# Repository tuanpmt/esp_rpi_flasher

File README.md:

# ESP32 RPI FLASHER

Language: [Việt Nam](./README.vi.md)

## Introduction

When mass-producing ESP32's products we need to have the tool to load the program for the product as quickly as possible. We have several ways to optimize and speed up loading binary firmware for ESP32 as follows:
- Flash multiple products at the same time
- Reduce the binary size
- Speed ​​up the UART baudrate
- Automate loading steps (automatically into bootloader mode ...)

ESP RPI FLASHER is a set of ESP32 multi-board load support tools at the same time including:
- High-speed USB-UART CP2102 board, supporting baudrate speed up to 2Mbps
- The program running on Raspberry Pi can use multiple CP2102 at the same time

The features of the program run on Raspberri Pi as follows:
- Automatically identify the CP2102 that is being connected (can plug multiple via USB port)
- Change firmware for ESP32 easily with configuration file
- Allow reflash failed boards.

## Prepare
* [Raspberry Pi 3 Model B/B+](https://www.raspberrypi.org)
* Thẻ nhớ 16GB
* [CP2102 USB UART board](./esp32_cp_programmer)
* Micro USB Cable, Button, LED, PCB prototype.

**Functianal button and LED**

|  | Function |
|:---:|:---:|
| Flash Button | Click to flash the program |
| Reflash Button | Click to re-flash the failed board |
| Reboot Button | Click to restart Raspberry |
| Flash LED | Report device loading program |
| Reflash LED | Report with loaded board failed |
| Ready LED | Raspberry are ready to be used |

## Steps

### Step 1: Connect device hardware

**Wire connections**

| | Raspberry Pin |
|:---:|:---:|
| Flash Button | 16 |
| Reflash Button | 20 |
| Reboot Button | 21 |
| Flash LED | 12 |
| Reflash LED | 7 |
| Ready LED | 8 |

The control circuit board after welding is fixed

### Step 2: Installing Raspbian for raspberry
* Download the latest Raspbian version [here](https://www.raspberrypi.org/downloads/raspbian/).
* Extract the downloaded file (the file after extracting has `.img` extension).
* Insert a memory card, open the terminal and execute the `sudo fdisk -l` command
* Determine the disk name when inserting a memory card, usually /dev/mmcblk0.
* Continue to execute the commands:
     * `cd Downloads /`
     * `sudo dd bs = 4M if = 2017-07-05-raspbian-jessie-lite.img of = /dev/mmcblk0`
* Note: The `cd Downloads/` command is used to go to the directory containing the installation file.
* Once done, we have a memory card that can boot Raspbian.

**Ref:** [Cách cài đặt hệ điều hành raspbian cho raspberry.](https://www.raspberrypi.org/documentation/installation/installing-images/)

**Setting Wifi and SSH to Raspberry PI**
* Remove the memory card and plug it back into the computer. At this time, The Linux/Ubuntu OS will mount 2 partitions, `boot` partition and `rootfs` partition.
* using `rootfs`, and open **/etc/wpa-supplicant/wpa-supplicant.conf** in this directory:
* Edit that file with this conntent:
```
ctrl_interface=DIR=/var/run/wpa_supplicant GROUP=netdev
update_config=1
network={
  ssid="your ssid"
  psk="your pass"
}
```

* Since November 2016, Raspberry has locked SSH when starting. To unlock SSH, create an `ssh` file (note: this file does not have an extension) in the boot partition of SD Card.
* Insert the memory card into RPI and wait for it to start in about 1 minute.
* Find the IP address of raspberry by logging in to the configuration page of WiFi Modem (for example: http://192.168.1.1). Almost all modems will display the DHCP Client list, find whichever host name is raspberrypi, get that IP, for example 192.168.1.12. In addition, some IP scanning software support such as [Angry IP Scanner](https://angryip.org/download/#mac).
* Open terminal up, ssh to raspberry's IP address: `ssh pi @ 192.168.1.12` and type the password:` raspberry` (Note the computer needs to use the same network with raspberry).
* So finished installing Raspbian for Raspberry Pi.

### Step 3: Install script

* Open the terminal, ssh by `ssh pi@192.168.1.12` with password: `raspberry`.
* Clone project: `git clone --recursive https://github.com/tuanpmt/esp_rpi_flasher.git`

**Note:** By default, the project needs to be saved in the **/home/pi** directory, if you want to save the script to another location, refer to [Configuring directory path](#Configuration-picture-path-letter-item).

* Install python and provide the firmware to the correct directory (using the `firmware_examples`):

```
sudo pip install -r requirements.txt
``` 

### Step 4: Set up auto-run script when raspberry starts
* After installing the raspberry script, check the current directory path with the command: `$PWD` (the default path is /home/pi/esp_rpi_flasher)
* Type `sudo nano /home/pi/.bashrc` to edit the **.Bashrc** file
* Add the following content to the last line of the file **.Bashrc**

```
echo Running at boot 
sudo /usr/bin/python3 /home/pi/esp_rpi_flasher/flasher.py &
```

With: `/home/pi/esp_rpi_flasher/flasher.py` is the default path of the project, if the script is saved in another location
* Nhấn **Ctrol** + **x** để save và reboot raspberry bằng lệnh `sudo reboot`.

Check out some more ways to run scripts when starting raspbian [here](https://www.dexterindustries.com/howto/run-a-program-on-your-raspberry-pi-at-startup/)

## Notes

The basic settings and firmware will be saved in the `/boot/firmware` path as follows:

```
boot
├──firmware
    ├──config.ini
    ├──encrypted
        ├──app-encrypted.bin
        ├──bootloader-reflash-digest-encrypted.bin
        ├──ota_data_initial-encrypted.bin
        ├──partitions-encrypted.bin
        ├──flash_encryption_key_1.0.0.alpha.4.bin
        ├──secure-bootloader-key-256.bin
    ├──normal
        ├──app.bin
        ├──bootloader.bin
        ├──ota_data_initial.bin
        ├──partitions.bin
```

Inside:
* **config.ini**: File stores configurations such as: LED pins, buttons and firmware paths, ...
* **encrypted**: The directory contains the encrypted firmware (used when loading programs that can boot boot and flash encryption).
* **normal**: The folder contains unencrypted firmware (used when loading regular programs).

### Secure boot and flash encryption
By default the script will load the program in the usual way (without secure boot and flash encryption). Enter the `/boot/firmware/` directory and open the `config.ini` file and edit `isEncrypt = True` to load the program to secure boot and flash encryption.

### Configure directory path
By default the script needs to be saved under the path `/home/pi` however, if you want to save the script in another directory you need to edit:
* When completing step 1, step 2, step 3, in the `/boot/firmware/` directory open the **config.ini** file and change the path of **projectPath**
* In step 4: Automatically run the script when starting raspbian, need to change the path to the **flasher.py** file

### Raspberry configuration and Button of Raspberry

LED and push button have been declared by default as Step 1 if you want to change the LED connector pins and Button with raspberry, proceed to the `/boot/firmware/` folder open the ** config.ini file ** and change the LED and Button pins accordingly.

## Video

## Ref

* [Raspberry Pi3 model B/B+](https://www.raspberrypi.org/products/raspberry-pi-3-model-b-plus/)
* [Install Raspbian for raspberry](https://www.raspberrypi.org/documentation/installation/installing-images/)
* [Five Ways To Run a Program On Raspberry Pi At Startup](https://www.dexterindustries.com/howto/run-a-program-on-your-raspberry-pi-at-startup/)
* [Wiring Fritzing](images/wiring.fzz)

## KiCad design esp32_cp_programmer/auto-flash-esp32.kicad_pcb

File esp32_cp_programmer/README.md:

# ESP32 Progammer

## Features

ESP32 Progammer
- Size: 22x30.5 mm.
- Intergrate micro USB.
- Input Voltage: 5v (Vusb).
- Open hardware with CC-BY-SA license.
- Design with KiCad.

## Hardware

### Schematics

### PCB Layout

### 3D

### Pinout 

### Fritzing part 

### Gerber

* [Gerber 1 board](./assets/auto-flash-esp32-22x36,5mm.zip)
* [Gerber panel 8 board](./assets/auto-flash-panel-8-board-94x71mm.zip)

### BOM 
| Component | Description | Part | References | Value | Footprint | Quantity Per PCB | link |
|-----------|-------------|------|------------|-------|-----------|------------------|-----------|
| 1 | Unpolarized capacitor | C	| C1 C2 C3 | 100nF | C_0603 | 3 | |	
| 2 | Unpolarized capacitor | C	| C4 C5	| 4.7uF	| C_0603 | 2 | |	
| 3 | LED generic | LED	| D1 D2 D3 | LED | LED_0603 | 3 | |	
| 4 | Generic connector, single row, 01x06 | Conn_01x06	| J3 | Conn_01x06 | Pin_Header_Straight_1x06_Pitch2.54mm | 1 | [link](https://item.taobao.com/item.htm?id=524060094118) |	
| 5 | Generic connector, single row, 01x08 | Conn_01x08	| J1 J2 | Conn_01x08 | Pin_Header_Straight_1x08_Pitch2.54mm | 2 | |	
| 6 | USB Micro Type B connector | USB_B_Micro	| J4 | USB_B_Micro | MicroUSB-B	| 1 | |	
| 7 | Transistor NPN (general) | Q_NPN_BEC | Q1 Q2 | Q_NPN_BEC | SOT-23_standar | 2 | |	
| 8 | Resistor | R | R2 R3 R4 | 10K | R_0603 | 3 | |	
| 9 | Resistor | R | R1	| 1K | R_0603 | 1 | |
| 10 | Resistor | R | R7 R8 R9 | 220 | R_0603 | 3 |  |	
| 11 | Resistor | R | R5 R6 | 470 | R_0603 | 2 | |
| 12 | | CP2102N | U1 | CP2102N | cp2102 | 1 | [link](https://item.taobao.com/item.htm?id=563461942639) |	

### Remark

This project was in development phase - we will remove this remark after release

# License

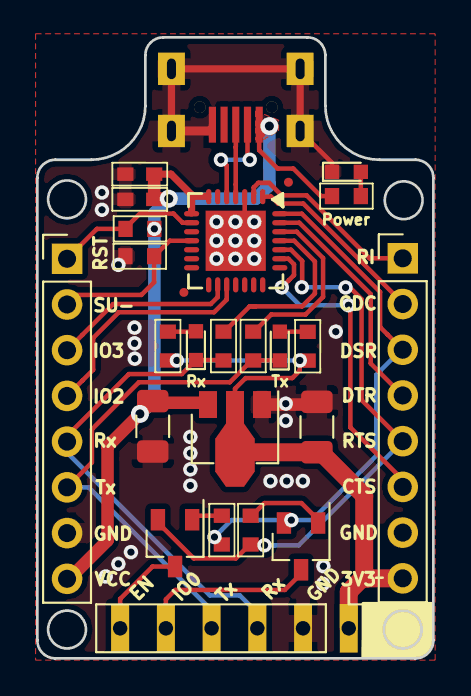
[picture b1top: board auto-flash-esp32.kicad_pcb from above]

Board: 2 copper layers, 22.0 x 34.5 mm, 24 parts (0 on the bottom side), 26 nets.

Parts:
C3: 0.1uF; C_0603
C4: 4.7uF; C_0603
C5, C6: C_Small; C_1206_3216Metric
D1, D2, D3: LED; LED_0603
J1, J2: Conn_01x08; Pin_Header_Straight_1x08_Pitch2.54mm
J3: Conn_01x06; Pin_Header_Straight_1x06_Pitch2.54mm
J4: USB_B_Micro; MicroUSB-B
Q1, Q2: Q_NPN_BEC; SOT-23_standar
R1: 1K; R_0603
R2, R3, R4: 10K; R_0603
R5, R6: 470; R_0603
R7, R8, R9: 220; R_0603
U1: CP2102N-28PIN; QFN-28-1EP_5x5mm_Pitch0.5mm
U2: AMS1117-3V3; SOT-89-3

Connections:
3V3: C6.1, J1.8, J3.1, R7.2, R8.2, U2.2
CTS: J1.6, U1.23
DCD: J1.2, U1.1
DSR: J1.4, U1.27
DTR: J1.3, Q2.2, R3.2, U1.28
EN: J3.6, Q1.3
GND: C3.2, C4.2, C5.2, C6.2, D3.1, J1.7, J2.7, J3.2, J4.5, R2.2, U1.3, U1.29, U2.1
IO0: J3.5, Q2.3
IO2/RS485: J2.4, U1.17
IO3/WU: J2.3, U1.16
unnamed: D1.2, R7.1
unnamed: D2.2, R8.1
unnamed: D3.2, R9.1
unnamed: J4.2, U1.5
unnamed: J4.3, U1.4
unnamed: Q1.1, R3.1
unnamed: Q2.1, R4.1
unnamed: R5.1, U1.26
unnamed: R6.1, U1.25
RESET: J2.1, R1.2, U1.9
RI: J1.1, U1.2
RTS: J1.5, Q1.2, R4.2, U1.24
Rx: D2.1, J2.5, J3.3, R6.2
SU-: J2.2, R2.1, U1.11
Tx: D1.1, J2.6, J3.4, R5.2
VCC: C3.1, C4.1, C5.1, J2.8, J4.1, R1.1, R9.2, U1.7, U1.8, U2.3

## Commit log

2018-10-14 Initial project
2019-02-12 Develop
2019-02-12 change code file and rename folder code
2019-02-13 Rename folder, remove pcb
    add English
    Change youtube url
    add pcb
    rm cp program
    Add hardware
2019-02-13 modify image
2019-02-13 fix the table display
2019-02-13 change pcb project name
2019-02-13 Change youtube link

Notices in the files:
esp32_cp_programmer/README.md:
License:
http://mirrors.creativecommons.org/presskit/buttons/88x31/png/by-sa.png
